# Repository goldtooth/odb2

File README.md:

View this project on [CADLAB.io](https://cadlab.io/project/1549). 

# odb

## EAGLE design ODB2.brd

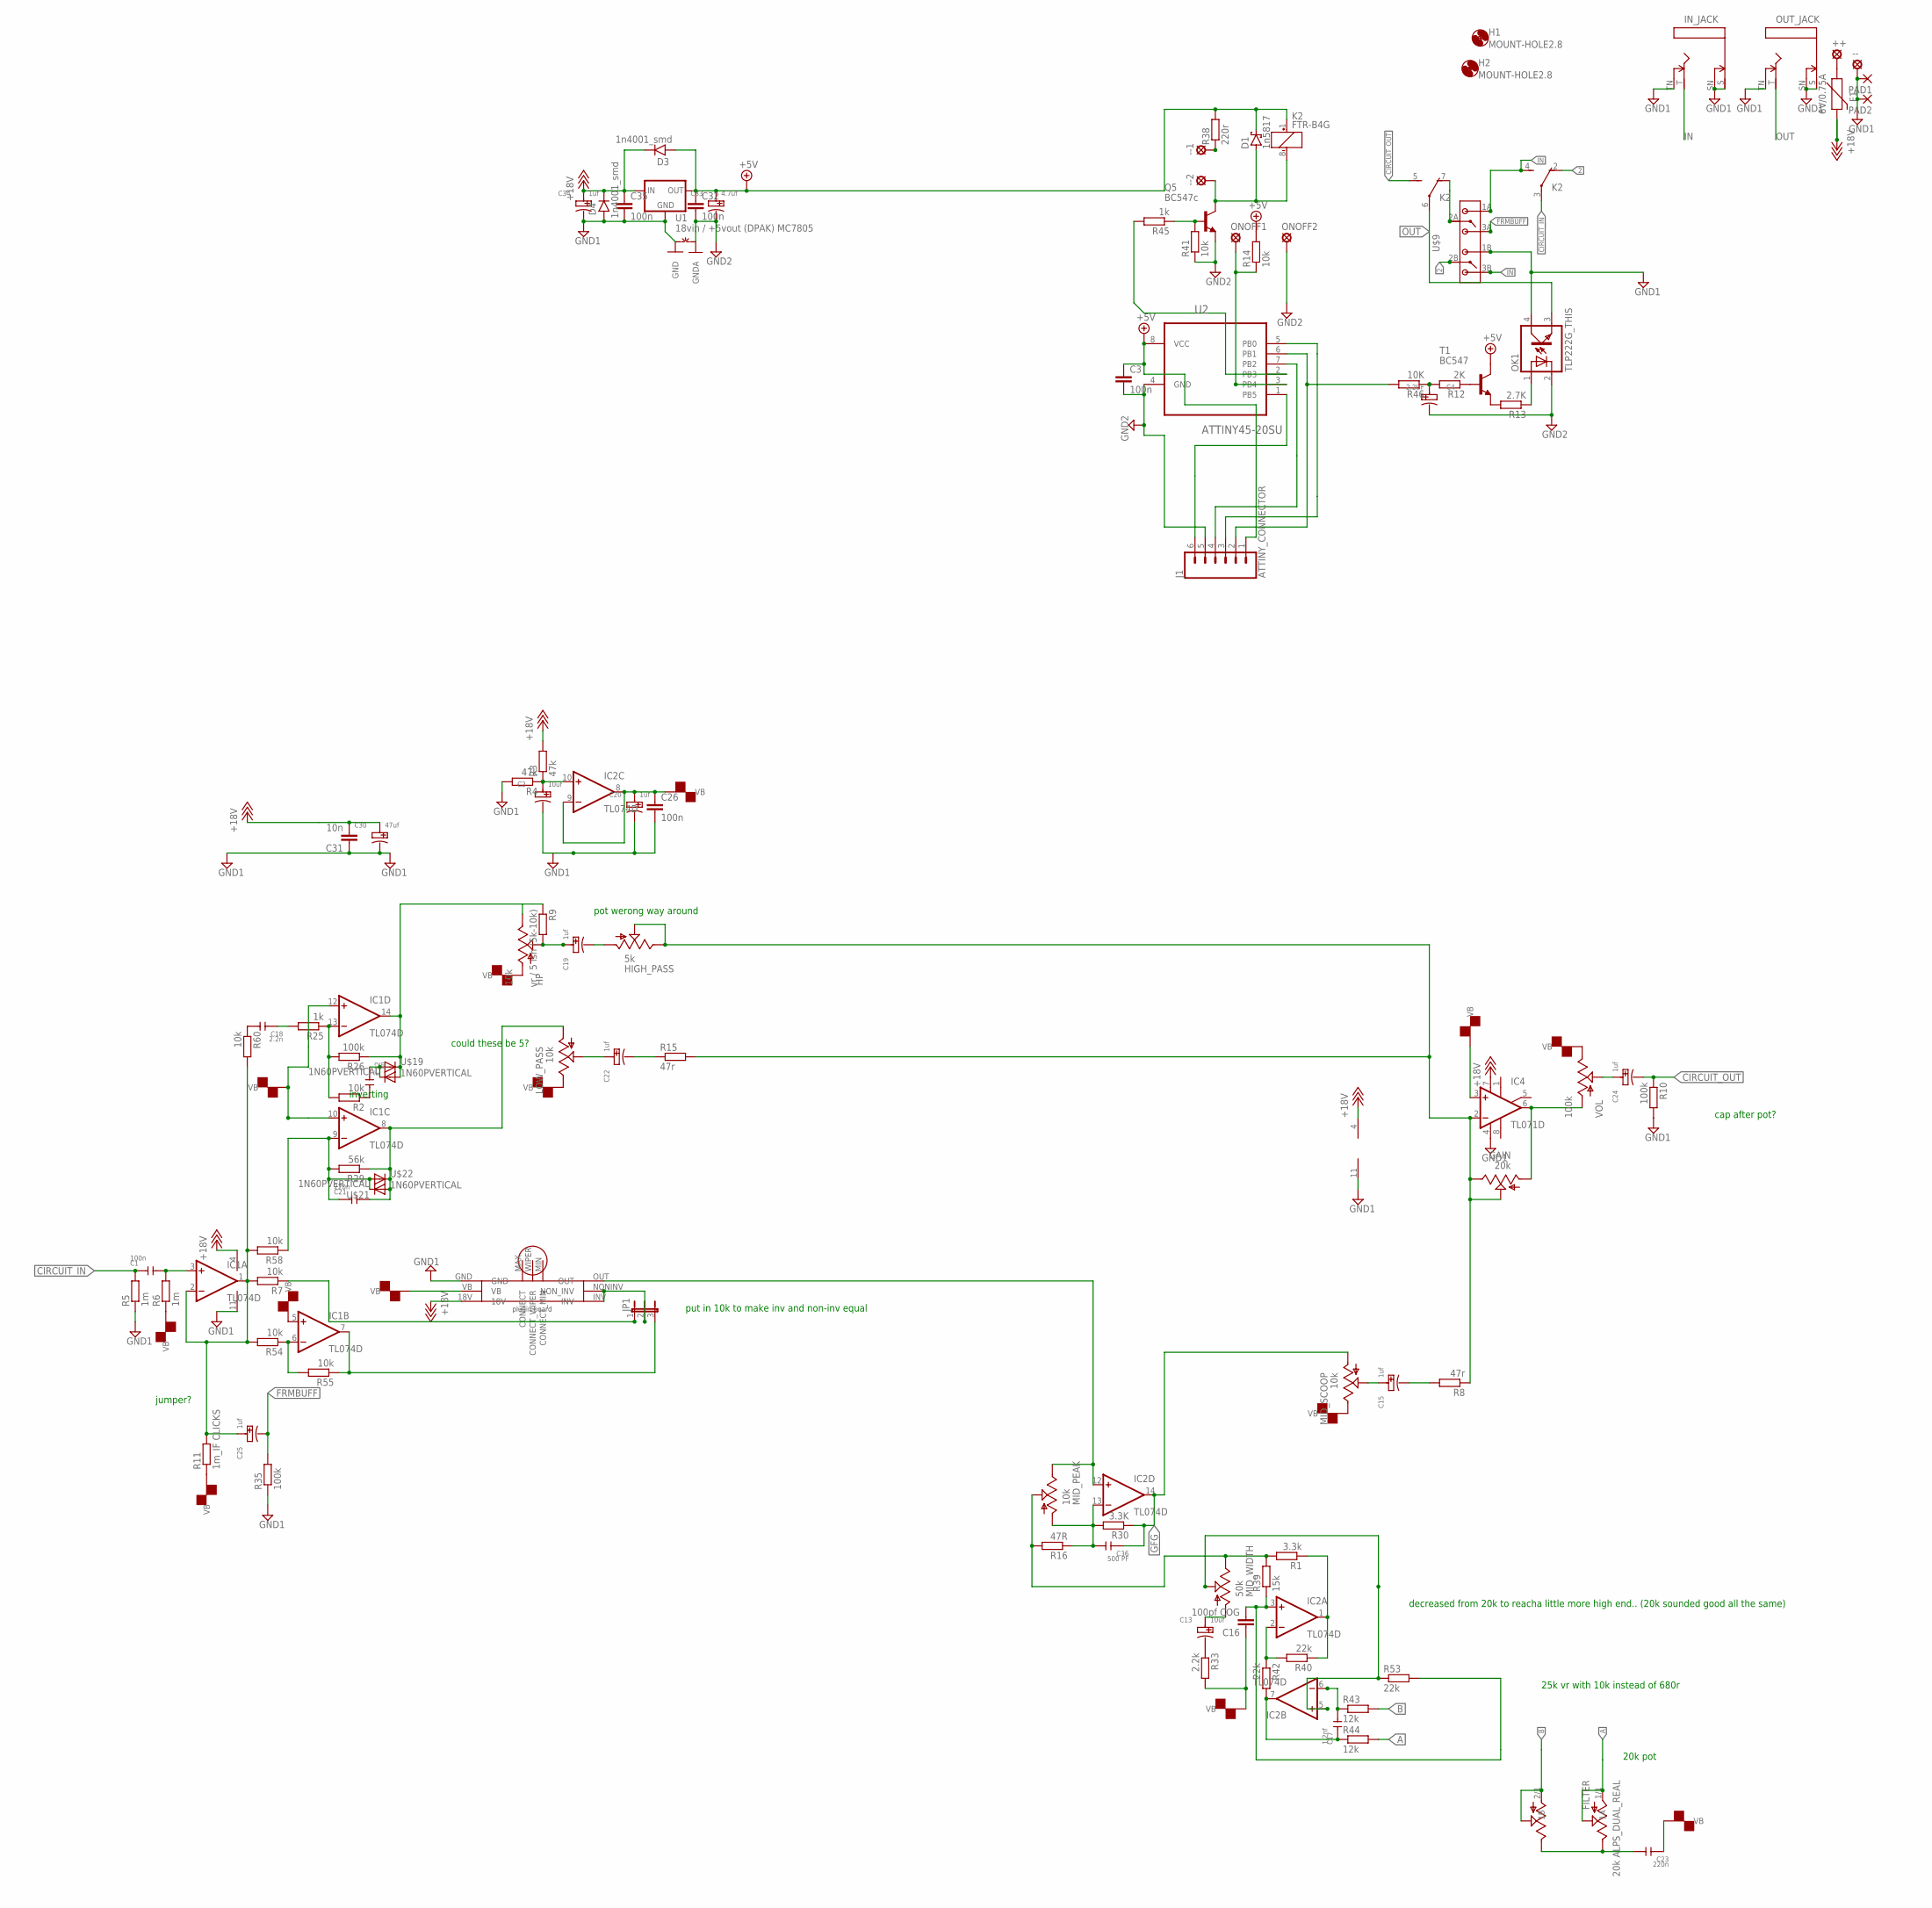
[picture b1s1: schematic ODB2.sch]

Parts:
++: LSP10
--, --1, --2: LSP10
C1: 100n; CERAMIC-5MM
C2, C13: 10uf; PC-D5.3MM
C3, C26, C32, C35: 100n; C1206
C4: 2.2UF; PC-D5.3MM
C12: 1n; CERAMIC-5MM
C15, C19, C20, C22, C24, C25, C34: 1uf; PC-D5.3MM
C16: 100pf COG; C1206
C17: 1.2nf; CERAMIC-5MM
C18: 2.2n; CERAMIC-5MM
C21, C23: 220n; CERAMIC-5MM
C30: 47uf; PC-D5.3MM
C31: 10n; C1206
C33: 4.7uf; PC-D5.3MM
C36: 500 PF; CERAMIC-5MM
D1: 1n5817; SMB
D3, D4: 1n4001_smd; DO41-1
F1: 6V/0.75A; 1206
FILTER: 20k ALPS_DUAL_REAL; ALPS_QUAD
GAIN: 20k; 3223G
H1, H2: MOUNT-HOLE2.8; 2,8
HIGH_PASS: 5k; 3223G
HP: 10k; ALPS_POT
IC1, IC2: TL074D; SO14
IC4: TL071D; SO08
IN_JACK: MMMONNNNOHOLES; MONONOHOLES
J1: ATTINY_CONNECTOR; 1X06_LONGPADS
JP1: JP2W
K2: FTR-B4G
LOW_PASS: 10k; 3223G
MID_PEAK: 10k; 3223G
MID_SCOOP: 10k; 3223G
MID_WIDTH: 50k; 3223G
OK1: TLP222G_THIS; DIL04
ONOFF1, ONOFF2: LSP10
OUT_JACK: MMMONNNNOHOLES; MONONOHOLES
PAD1, PAD2: SMD5; SMD2,54-5,08
Q5: BC547c; TO92
R1: 3.3k; R1206
R2, R7, R54, R55, R58, R60: 10k; R1206
R3, R4: 47k; R1206
R5, R6: 1m; R1206
R8, R15: 47r; R1206
R9: vr / 5 ish (5k-10k); R1206
R10, R26, R35: 100k; R1206
R11: 1m_IF CLICKS; R1206
R12: 2K; M1206
R13: 2.7K; M1206
R14, R41: 10k; M1206
R16: 47R; R1206
R25: 1k; R1206
R29: 56k; R1206
R30: 3.3K; R1206
R33: 2.2k; R1206
R38: 220r; M1206
R39: 15k; R1206
R40, R42, R53: 22k; R1206
R43, R44: 12k; R1206
R45: 1k; M1206
R46: 10K; M1206
T1: BC547; TO92
U1: 18vin / +5vout (DPAK) MC7805; TO-252
U2: ATTINY45-20SU; SOIC127P798X216-8N
U$5: GT_PLUGIN_ODB; PLUGIN_RECIEVE_ANOTHER
U$9: BYSWITCH; BUFF/TRBYPASS
U$19, U$20, U$21, U$22: 1N60PVERTICAL; DO41-1
VOL: 100k; ALPS_POT
~NUDEV~1: GND-GNDA1,27MM; GND-GNDA-1,27MM

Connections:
2: K2.2 (O), U$9.2B
+5V: C3.1, C32.1, C33.+, D1.C, D3.A, J1.1, K2.1 (+), R14.2, R38.2, T1.3 (C), U1.2 (OUT), U2.8 (VCC)
+18V: C30.+, C31.2, C34.+, C35.1, D3.C, D4.C, F1.2, IC1.4 (V+), IC2.4 (V+), IC4.7 (V+), R3.2, U1.1 (IN), U$5.18V
A: FILTER.1/1 (1A), FILTER.1/2 (2A), R44.2
B: FILTER.2/1 (1B), FILTER.2/2 (2B), R43.2
CIRCUIT_IN: C1.1, K2.3, R5.2
CIRCUIT_OUT: C24.-, K2.5 (S), R10.1
FRMBUFF: C25.-, R35.2, U$9.3A
GFG: C36.1, IC2.14 (OUT), MID_SCOOP.1 (A), R30.1
GND1: --.MP, C2.-, C20.-, C26.2, C30.-, C31.1, C34.-, C35.2, D4.A, IC1.11 (V-), IC2.11 (V-), IC4.4 (V-), IN_JACK.S, IN_JACK.SN, IN_JACK.TN, OK1.4 (COL), OUT_JACK.S, OUT_JACK.SN, OUT_JACK.TN, PAD1.1, PAD2.1, R4.2, R5.1, R10.2, R35.1, U1.3 (GND), U$5.GND, U$9.1B, ~NUDEV~1.GND
GND2: C3.2, C4.-, C32.2, C33.-, J1.5, OK1.2 (C), ONOFF2.MP, Q5.1 (E), R41.1, U2.4 (GND), ~NUDEV~1.GNDA
IN: IN_JACK.T, K2.4 (S), U$9.1A, U$9.3B
unnamed: C4.+, R12.2, R46.1
unnamed: R12.1, T1.2 (B)
unnamed: C2.+, IC2.10 (+IN), R3.1, R4.1
unnamed: R13.2, T1.1 (E)
unnamed: C1.2, IC1.3 (+IN), R6.2
unnamed: JP1.1, R7.1
unnamed: C15.+, MID_SCOOP.2 (S)
unnamed: C22.+, LOW_PASS.2 (S)
unnamed: ++.MP, F1.1
unnamed: C22.-, R15.1
unnamed: C12.1, U$19.A, U$20.C
unnamed: C19.-, HIGH_PASS.1 (A)
unnamed: C15.-, R8.2
unnamed: JP1.2, U$5.INV, U$5.NONINV (NON_INV)
unnamed: C24.+, VOL.P$2 (S)
unnamed: IC1.7 (OUT), JP1.3, R55.1
unnamed: C12.2, R2.1
unnamed: C25.+, IC1.1 (OUT), IC1.2 (-IN), R7.2, R11.2, R54.2, R58.2, R60.2
unnamed: C36.2, IC2.13 (-IN), MID_PEAK.1 (A), R16.1, R30.2
unnamed: HP.P$1 (E), IC1.14 (OUT), R9.1, R26.1, U$19.C, U$20.A
unnamed: MID_PEAK.2 (S), MID_WIDTH.3 (E), R1.2, R16.2, R39.2
unnamed: C19.+, HP.P$2 (S), R9.2
unnamed: C18.2, R60.1
unnamed: C13.+, MID_WIDTH.1 (A)
unnamed: C13.-, R33.1
unnamed: C16.2, IC2.3 (+IN), R39.1, R53.2
unnamed: IC2.5 (+IN), MID_WIDTH.2 (S), R53.1
unnamed: C18.1, R25.2
unnamed: C23.2, FILTER.1/3 (3A), FILTER.2/3 (3B)
unnamed: IC1.13 (-IN), R2.2, R25.1, R26.2
unnamed: IC2.1 (OUT), R1.1, R40.1
unnamed: C17.1, IC2.7 (OUT), R42.2, R44.1
unnamed: IC2.2 (-IN), R40.2, R42.1
unnamed: C17.2, IC2.6 (-IN), R43.1
unnamed: C21.2, IC1.8 (OUT), LOW_PASS.1 (A), R29.1, U$21.A, U$22.C
unnamed: GAIN.2 (S), GAIN.3 (E), HIGH_PASS.2 (S), HIGH_PASS.3 (E), IC4.2 (-IN), R8.1, R15.2
unnamed: K2.7 (O), U$9.2A
unnamed: C21.1, IC1.9 (-IN), R29.2, R58.1, U$21.C, U$22.A
unnamed: GAIN.1 (A), IC4.6 (OUT), VOL.P$3 (A)
unnamed: J1.3, U2.5 (PB0)
unnamed: J1.2, R46.2, U2.6 (PB1)
unnamed: J1.4, U2.7 (PB2)
unnamed: J1.6, U2.1 (PB5)
unnamed: --1.MP, R38.1
unnamed: --2.MP, D1.A, K2.8 (-), Q5.3 (C)
unnamed: IC2.12 (+IN), MID_PEAK.3 (E), U$5.OUT
unnamed: IC1.6 (-IN), R54.1, R55.2
unnamed: Q5.2 (B), R41.2, R45.1
unnamed: R45.2, U2.2 (PB3)
unnamed: ONOFF1.MP, R14.1, U2.3 (PB4)
unnamed: OK1.1 (A), R13.1
OUT: K2.6, OK1.3 (EMIT), OUT_JACK.T
VB: C16.1, C20.+, C23.1, C26.1, HP.P$3 (A), IC1.5 (+IN), IC1.10 (+IN), IC1.12 (+IN), IC2.8 (OUT), IC2.9 (-IN), IC4.3 (+IN), LOW_PASS.3 (E), MID_SCOOP.3 (E), R6.1, R11.1, R33.2, U$5.VB, VOL.P$1 (E)

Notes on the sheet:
jumper?
could these be 5?
inverting
25k vr with 10k instead of 680r
20k pot
put in 10k to make inv and non-inv equal
pot werong way around
cap after pot?
decreased from 20k to reacha little more high end.. (20k sounded good all the same)

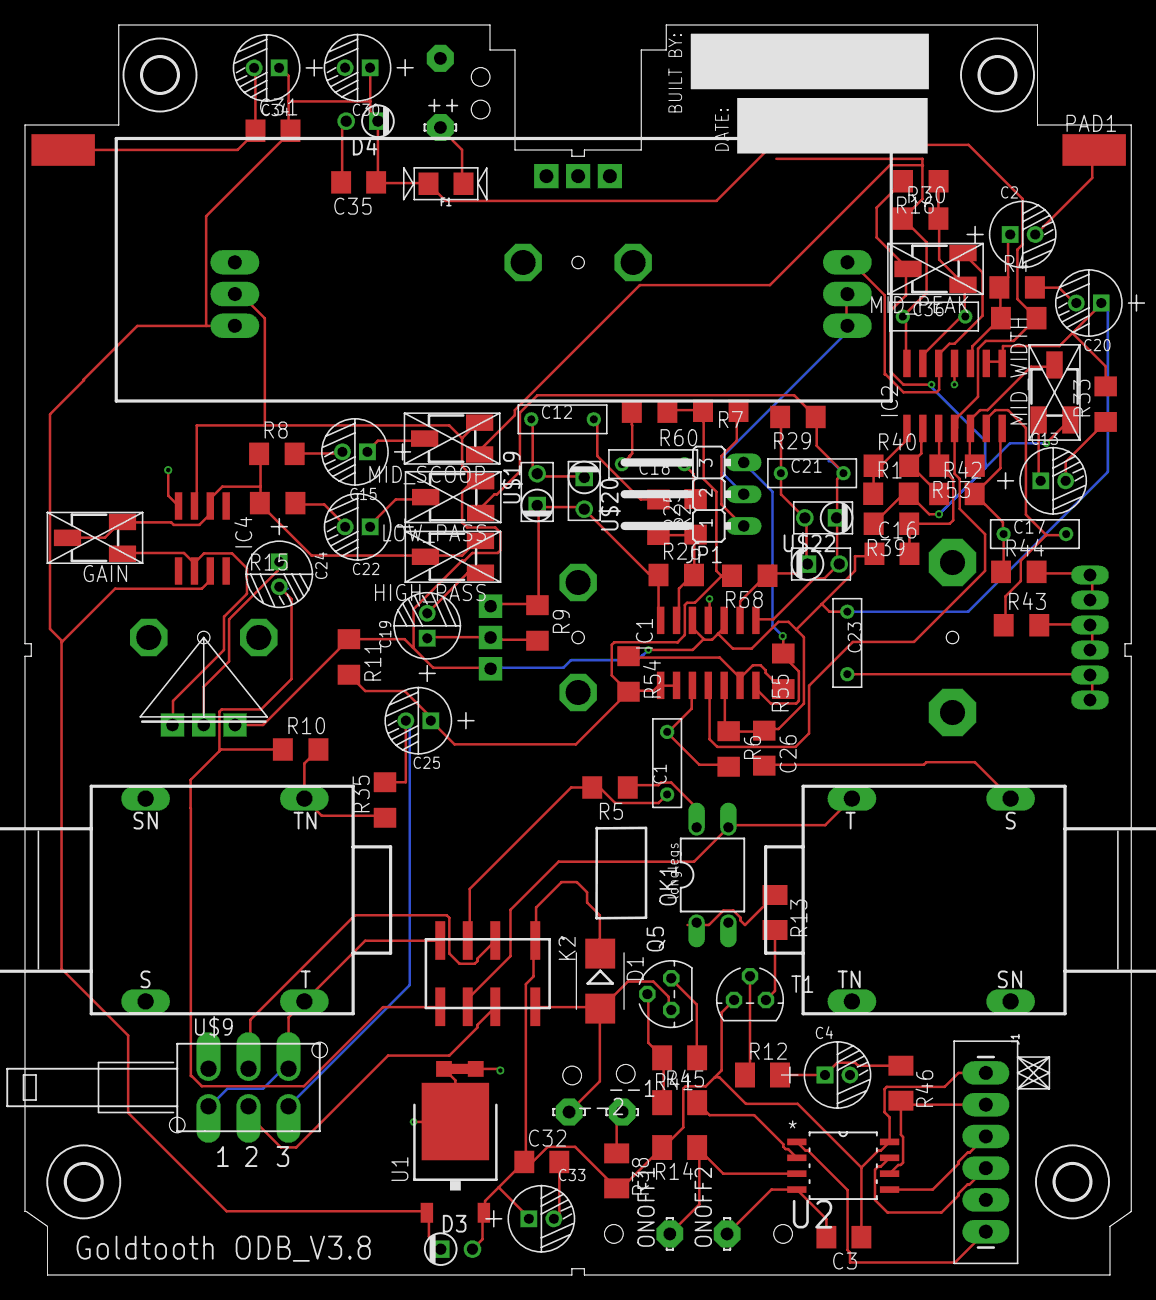
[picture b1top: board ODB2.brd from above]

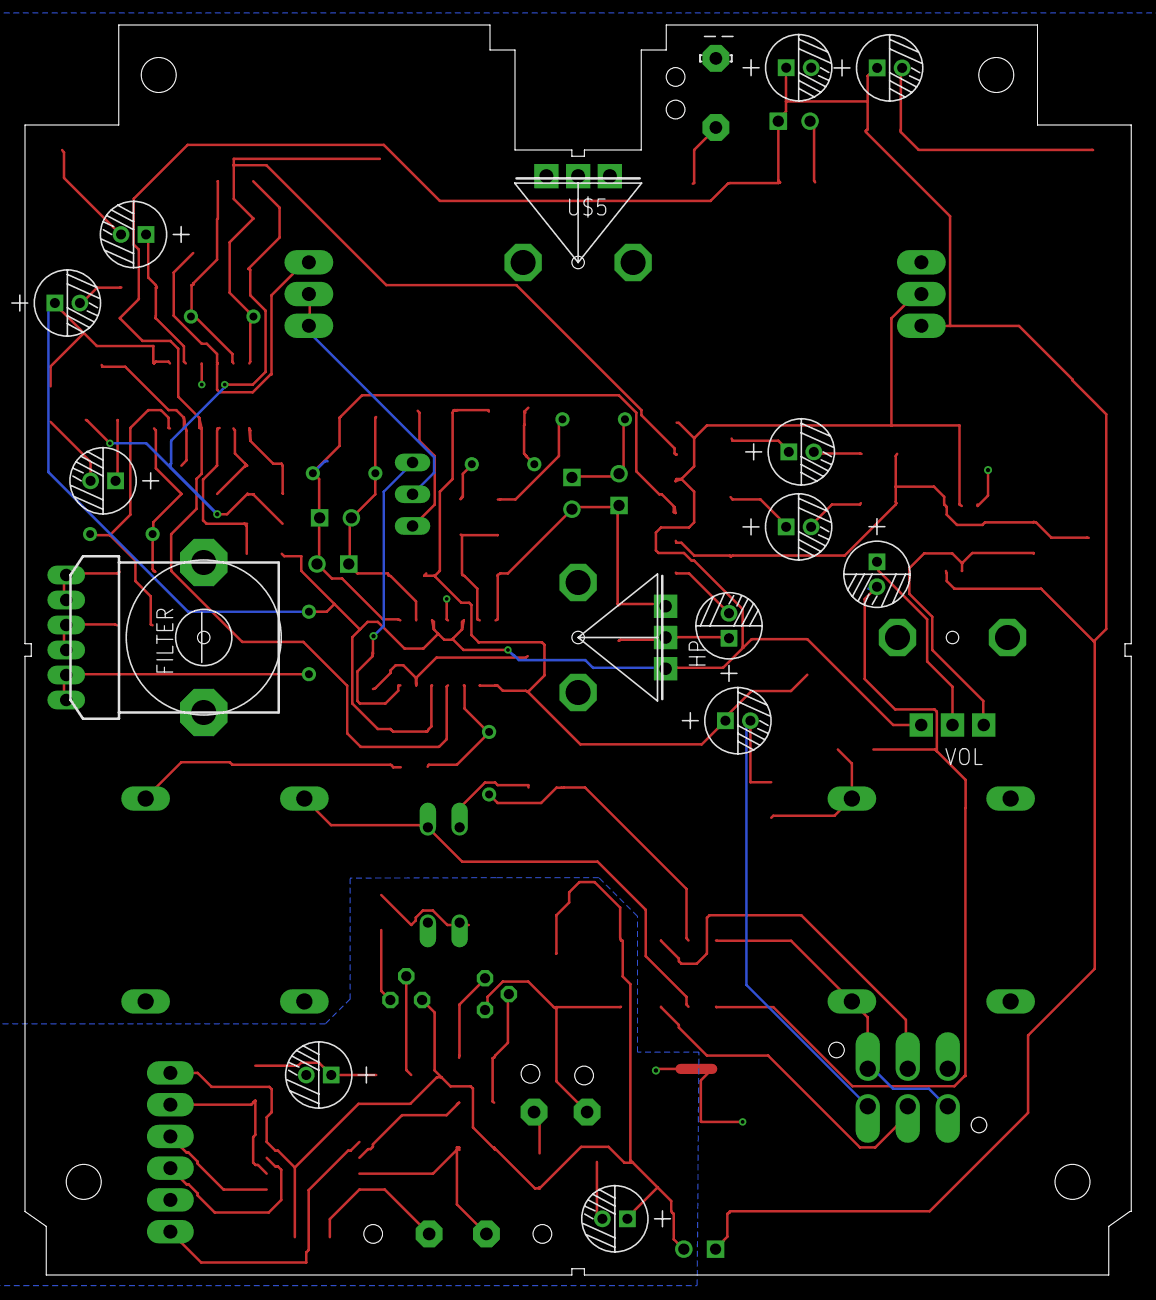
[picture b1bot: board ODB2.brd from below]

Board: 2 copper layers, 88.5 x 100.0 mm, 112 parts (3 on the bottom side), 65 nets.

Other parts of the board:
H3, H4: MOUNT-HOLE2.8; 2,8
U$1, U$2, U$15, U$16, U$17, U$18: HOLD

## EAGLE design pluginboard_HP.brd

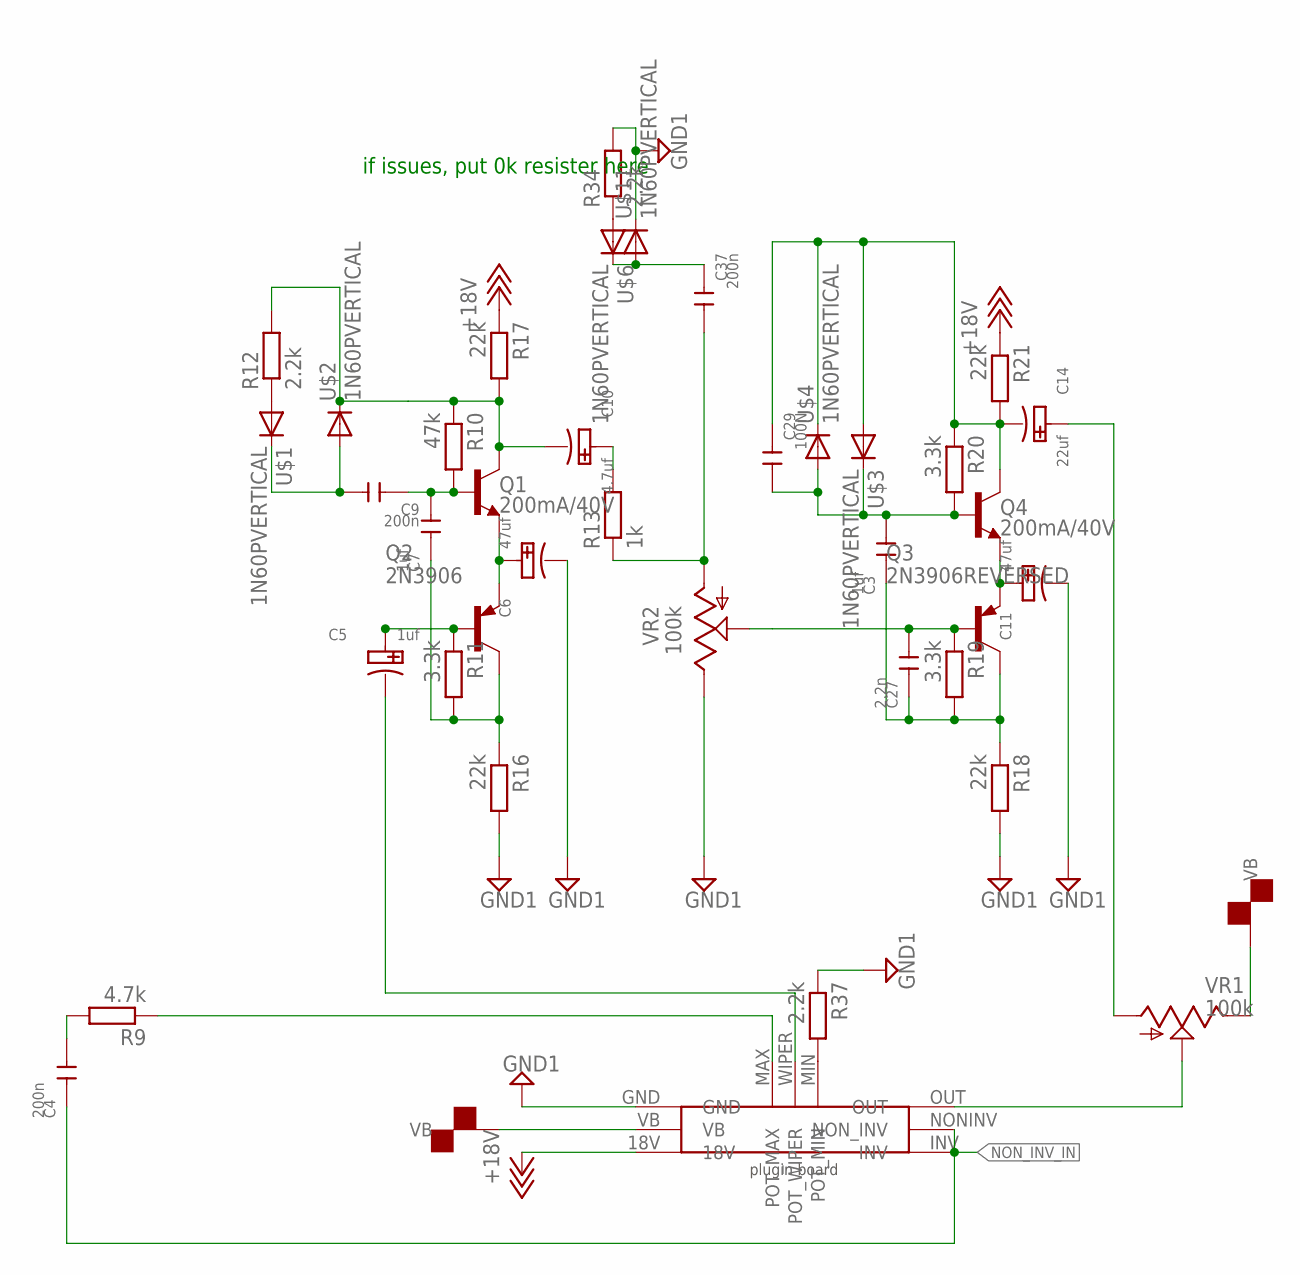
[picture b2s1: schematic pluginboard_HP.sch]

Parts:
C3, C7: 1uf; CERAMIC-5MM
C4, C9, C37: 200n; CERAMIC-5MM
C5: 1uf; PC-D5.3MM
C6, C11: 47uf; PC-D5.3MM
C10: 4.7uf; PC-D5.3MM
C14: 22uf; PC-D5.3MM
C27: 2.2n; CERAMIC-5MM
C29: 100N; CERAMIC-5MM
Q1, Q4: 200mA/40V; TO-92
Q2: 2N3906; TO92
Q3: 2N3906REVERSED
R9: 4.7k; R1206
R10: 47k; R1206
R11, R19, R20: 3.3k; R1206
R12, R34, R37: 2.2k; R1206
R13: 1k; R1206
R16, R17, R18, R21: 22k; R1206
U$1, U$2, U$3, U$4, U$6, U$11: 1N60PVERTICAL; DO41-1
U$9: GT_BOARD; PLUGIN_BOARD
VR1, VR2: 100k; 3223G

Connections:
+18V: R17.1, R21.1, U$9.18V
BB_OUT1: U$9.OUT, VR1.2 (S)
GND1: C6.-, C11.-, R16.2, R18.2, R34.2, R37.1, U$9.GND, U$11.C, VR2.3 (E)
unnamed: C6.+, Q1.1 (E), Q2.3 (E)
unnamed: C14.+, VR1.1 (A)
unnamed: R12.1, U$1.A
unnamed: C9.2, U$1.C, U$2.A
unnamed: R37.2, U$9.MIN (POT_MIN)
unnamed: C4.2, R9.2
unnamed: R9.1, U$9.MAX (POT_MAX)
unnamed: C5.-, U$9.WIPER (POT_WIPER)
unnamed: C5.+, Q2.2 (B), R11.1
unnamed: C7.2, C9.1, Q1.2 (B), R10.2
unnamed: C7.1, Q2.1 (C), R11.2, R16.1
unnamed: C37.2, R13.1, VR2.1 (A)
unnamed: C10.-, Q1.3 (C), R10.1, R12.2, R17.2, U$2.C
unnamed: C11.+, Q3.3 (E), Q4.1 (E)
unnamed: C10.+, R13.2
unnamed: C3.1, C27.1, Q3.1 (C), R18.1, R19.2
unnamed: C27.2, Q3.2 (B), R19.1, VR2.2 (S)
unnamed: C3.2, C29.2, Q4.2 (B), R20.2, U$3.C, U$4.A
unnamed: R34.1, U$6.A
unnamed: C37.1, U$6.C, U$11.A
unnamed: C14.-, C29.1, Q4.3 (C), R20.1, R21.2, U$3.A, U$4.C
NON_INV_IN: C4.1, U$9.INV, U$9.NONINV (NON_INV)
VB: U$9.VB, VR1.3 (E)

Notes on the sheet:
if issues, put 0k resister here

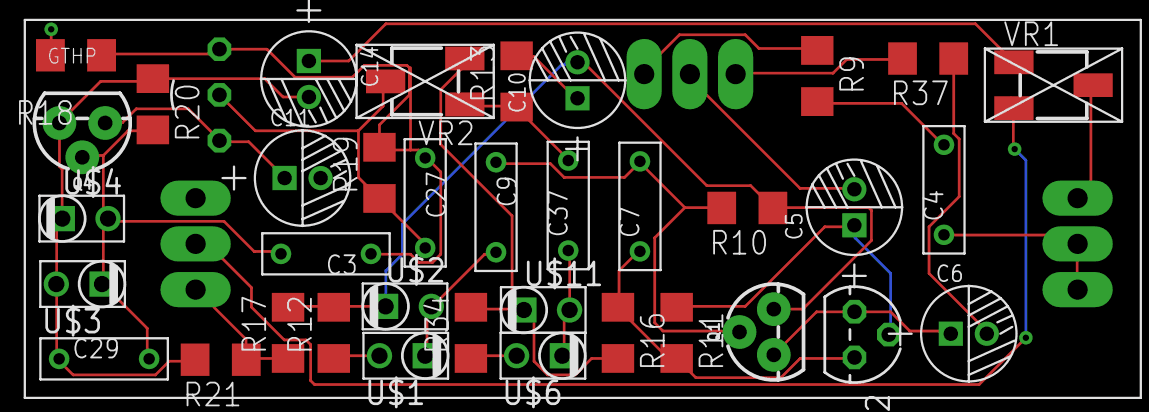
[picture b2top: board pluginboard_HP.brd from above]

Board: 2 copper layers, 38 parts (1 on the bottom side), 26 nets.

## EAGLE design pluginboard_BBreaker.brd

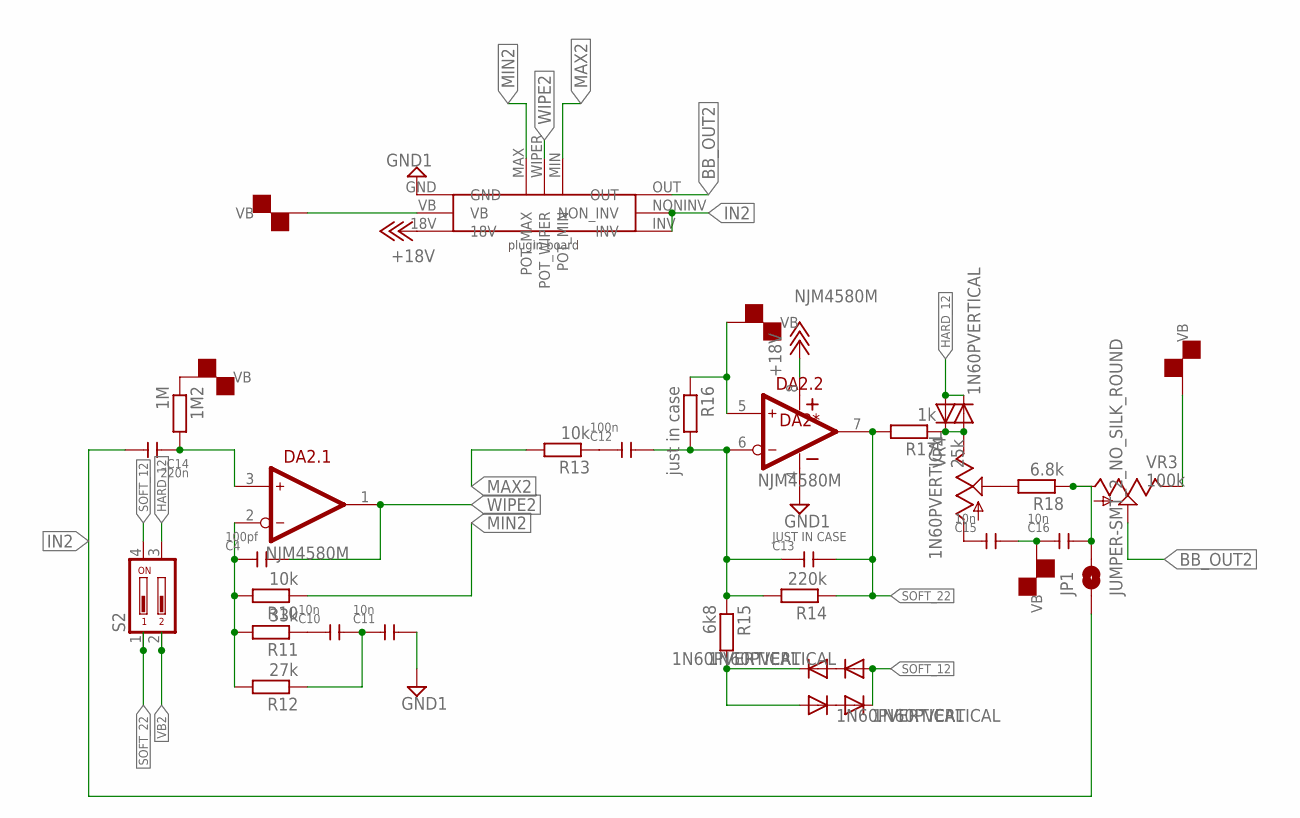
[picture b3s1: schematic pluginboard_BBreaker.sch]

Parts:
1M2: 1M; R1206
C4: 100pf; CERAMIC-5MM
C10, C11, C15, C16: 10n; CERAMIC-5MM
C12: 100n; CERAMIC-5MM
C13: JUST IN CASE; CERAMIC-5MM
C14: 220n; CERAMIC-5MM
DA2: NJM4580M; SO-8
JP1: JUMPER-SMT_2_NO_SILK_ROUND; SMT-JUMPER_2_NO_SILK_ROUND
R10, R13: 10k; R1206
R11: 33k; R1206
R12: 27k; R1206
R14: 220k; R1206
R15: 6k8; R1206
R16: just in case; R1206
R17: 1k; R1206
R18: 6.8k; R1206
S2: DP02; DP-02
U$13, U$14, U$15, U$16, U$20, U$21: 1N60PVERTICAL; DO41-1
U$22: GT_BOARD; PLUGIN_BOARD
VR3: 100k; 3223G
VR4: 25k; 3223G

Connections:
+18V2: DA2.8 (V+), U$22.18V
BB_OUT2: U$22.OUT, VR3.2 (S)
GND12: C11.2, DA2.4 (V-), U$22.GND
HARD_12: S2.3, U$20.A, U$21.C
IN2: C14.2, JP1.1, U$22.INV, U$22.NONINV (NON_INV)
MAX2: R13.2, U$22.MIN (POT_MIN)
MIN2: R10.1, U$22.MAX (POT_MAX)
unnamed: C10.1, R11.1
unnamed: C10.2, C11.1, R12.1
unnamed: C12.1, R13.1
unnamed: C12.2, C13.1, DA2.6 (IN-), R14.2, R15.1, R16.2
unnamed: U$13.C, U$14.A
unnamed: U$15.C, U$16.A
unnamed: R15.2, U$14.C, U$15.A
unnamed: C4.1, DA2.2 (IN-), R10.2, R11.2, R12.2
unnamed: R17.1, U$20.C, U$21.A, VR4.3 (E)
unnamed: 1M2.2, C14.1, DA2.3 (IN+)
unnamed: R18.2, VR4.2 (S)
unnamed: C16.2, JP1.2, R18.1, VR3.1 (A)
unnamed: C15.1, VR4.1 (A)
SOFT_12: S2.4, U$13.A, U$16.C
SOFT_22: C13.2, DA2.7 (OUT), R14.1, R17.2, S2.1
VB2: 1M2.1, C15.2, C16.1, DA2.5 (IN+), R16.1, S2.2, U$22.VB, VR3.3 (E)
WIPE2: C4.2, DA2.1 (OUT), U$22.WIPER (POT_WIPER)

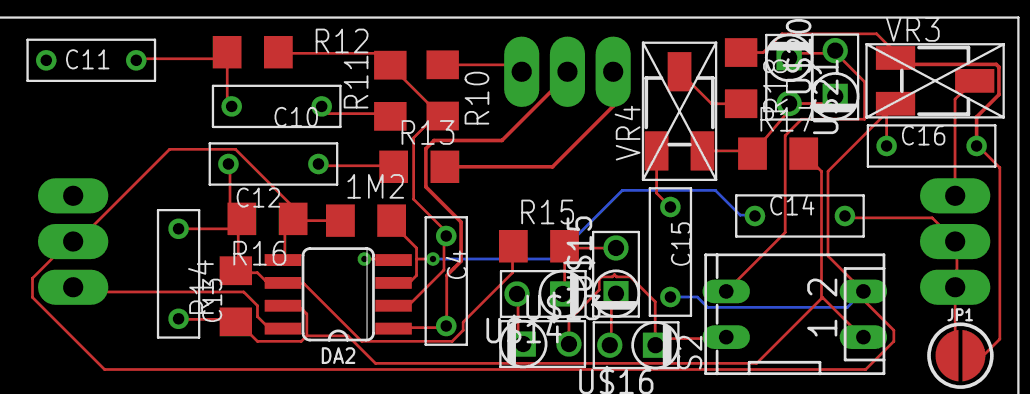
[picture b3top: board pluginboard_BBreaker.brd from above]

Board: 2 copper layers, 30 parts (0 on the bottom side), 24 nets.

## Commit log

2019-01-07 Initial
2019-01-07 Backlink to CADLAB.io has been added.
2019-01-08 V3.2
    ADDED SWITCH TO REVERSE TRANSITOR
    REMOVED 1 CAPACITOR ON FILTER
    ADDED SILKSCREEN TO OPTIONAL AREA AROUND CLIPPING ON OUTPUT STAGE
2019-01-08 Update ODB2.brd
    Change of Silkscreen on optional parts
2019-01-08 reverted back
    and tidied transistor to correct orientation on reverse
2019-01-08 ready to go
2019-01-20 v3.3
    added board notch, diodes on HP AND LP
2019-03-04 big changes
2019-03-11 new board
2019-03-12 ordered 120119
2019-04-11 various
2019-04-29 5sdf
2019-06-23 NEW WITH SILENT SWITCHING

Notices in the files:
parts and their libraries:
SparkFun-IC-Power: Licensing: Creative Commons ShareAlike 4.0 International - https://creativecommons.org/licenses/by-sa/4.0
